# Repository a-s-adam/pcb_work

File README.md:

Working with JDM product development structures, it's hard to get full exposure on an entire electrical PCB design from start to finish. The goal of this repository is to display design, component selection, schematic capture, layout, ordering, and bring-up without sharing designs done during my 9-5 job.

dev_board
- Working to redefine scope of this board; originally it was ATMEGA which is less common in production boards, so I'm exploring ESP32 based system to make an IoT mesh network.
- [Work in Progress]

MixSigBoard
- STM32 Based board with 2 SPI interfaces (ADC,DAC), ADC input, DAC output, a few GPIO's via RGB LED's, and Software Debug (SWD) interface.
- Analog Bias Generator, anti-aliasing filters, power supply line filtering, USB-C 2.0 compatibility
- Ground via next to all signal vias to give short return path and reduce EMI
- Fan out of traces where possible to reduce cross talk
- PHYSICAL separation of analog and digital components (placing A&D components far apart from each other has best results of reducing noise between the two) https://www.youtube.com/watch?v=ySuUZEjARPY
- Stitching Vias placed throughout board (2.5 mm grid)
- Silkscreen labeling of circuit portions
- Included Gerber, BOM, footprints,symbols, drill files

FPGA_Board
- AMD Zynq-7000 based board: https://docs.amd.com/v/u/en-US/zynq-7000-product-selection-guide [XC7Z010-2CLG400I]
- Config Memory is determined by FPGA chosen: https://docs.amd.com/r/en-US/ug908-vivado-programming-debugging/Virtex-UltraScale-Configuration-Memory-Devices?tocId=SfnAO9Qdpk7bcqPQwSsYiQ
- BGA Routing Application Manual: https://docs.amd.com/r/en-US/ug1099-bga-device-design-rules/Introduction
- Stack-up Selection for Various Layer PCB's https://www.pcbway.com/multi-layer-laminated-structure.html
- [Work in Progress]

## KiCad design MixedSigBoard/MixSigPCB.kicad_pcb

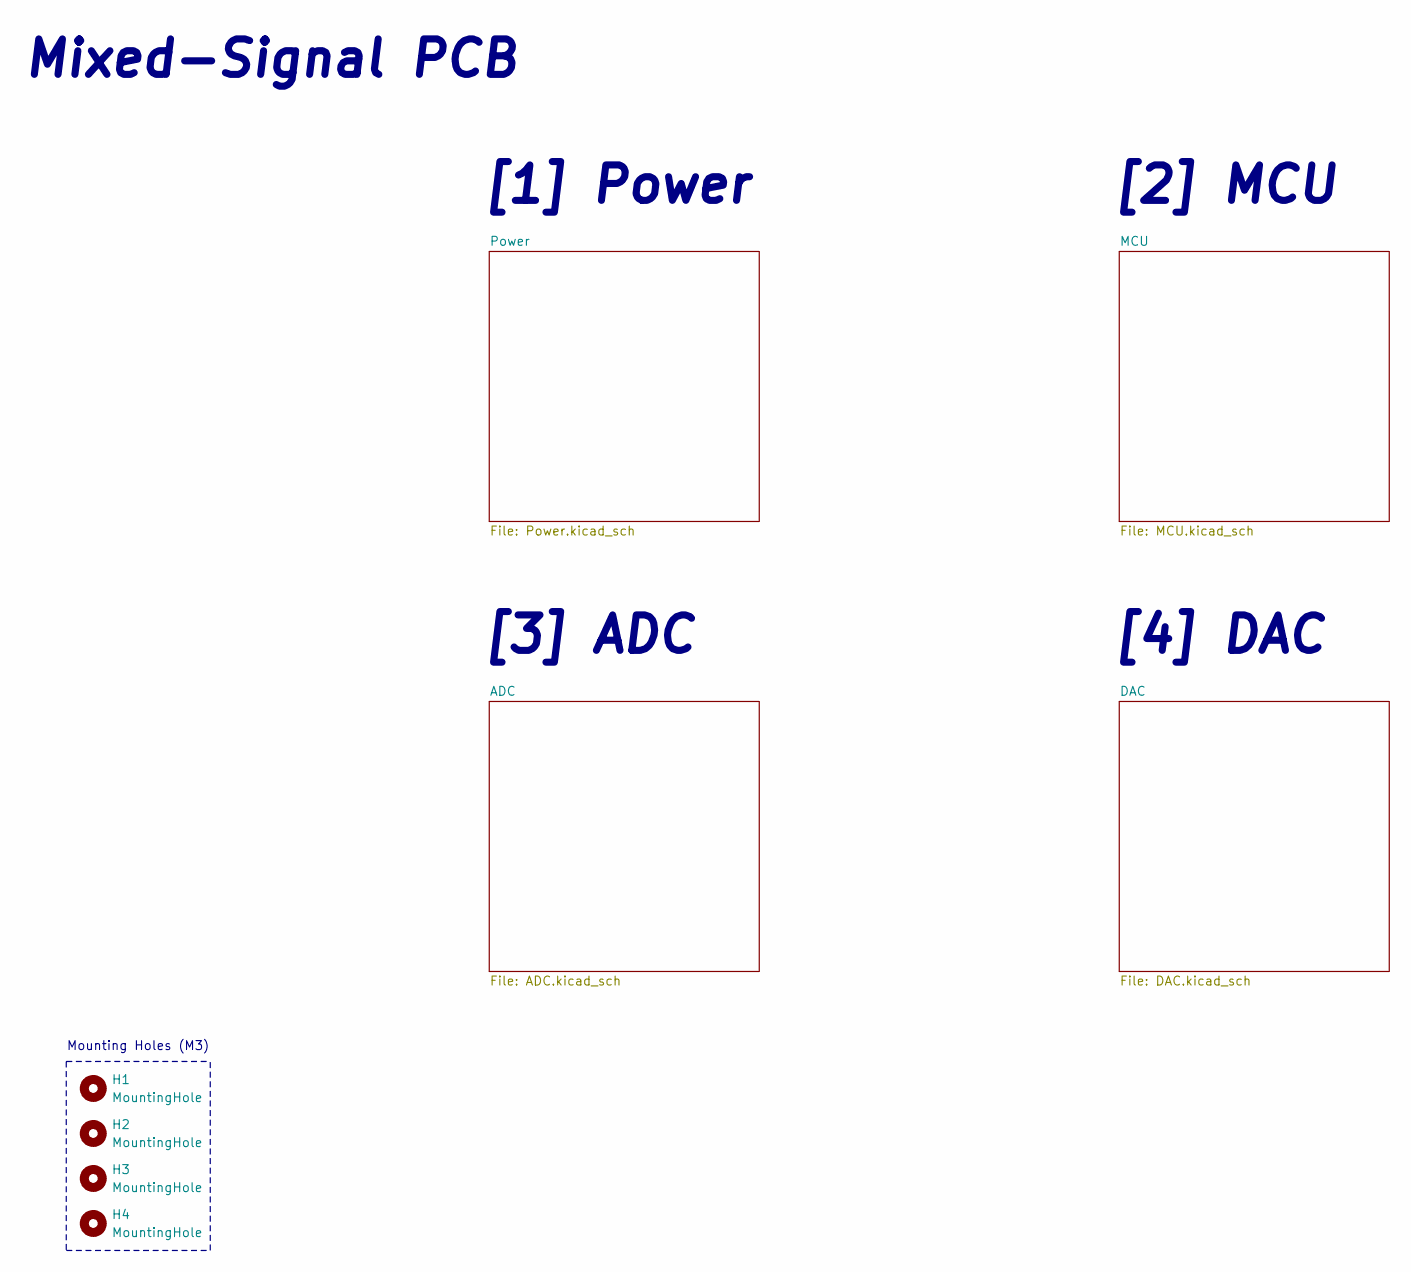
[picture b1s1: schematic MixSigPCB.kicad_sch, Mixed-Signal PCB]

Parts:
H1, H2, H3, H4: MountingHole; MountingHole_3.2mm_M3

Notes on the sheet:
[4] DAC
Mixed-Signal PCB
[3] ADC
Mounting Holes (M3)
[2] MCU
[1] Power

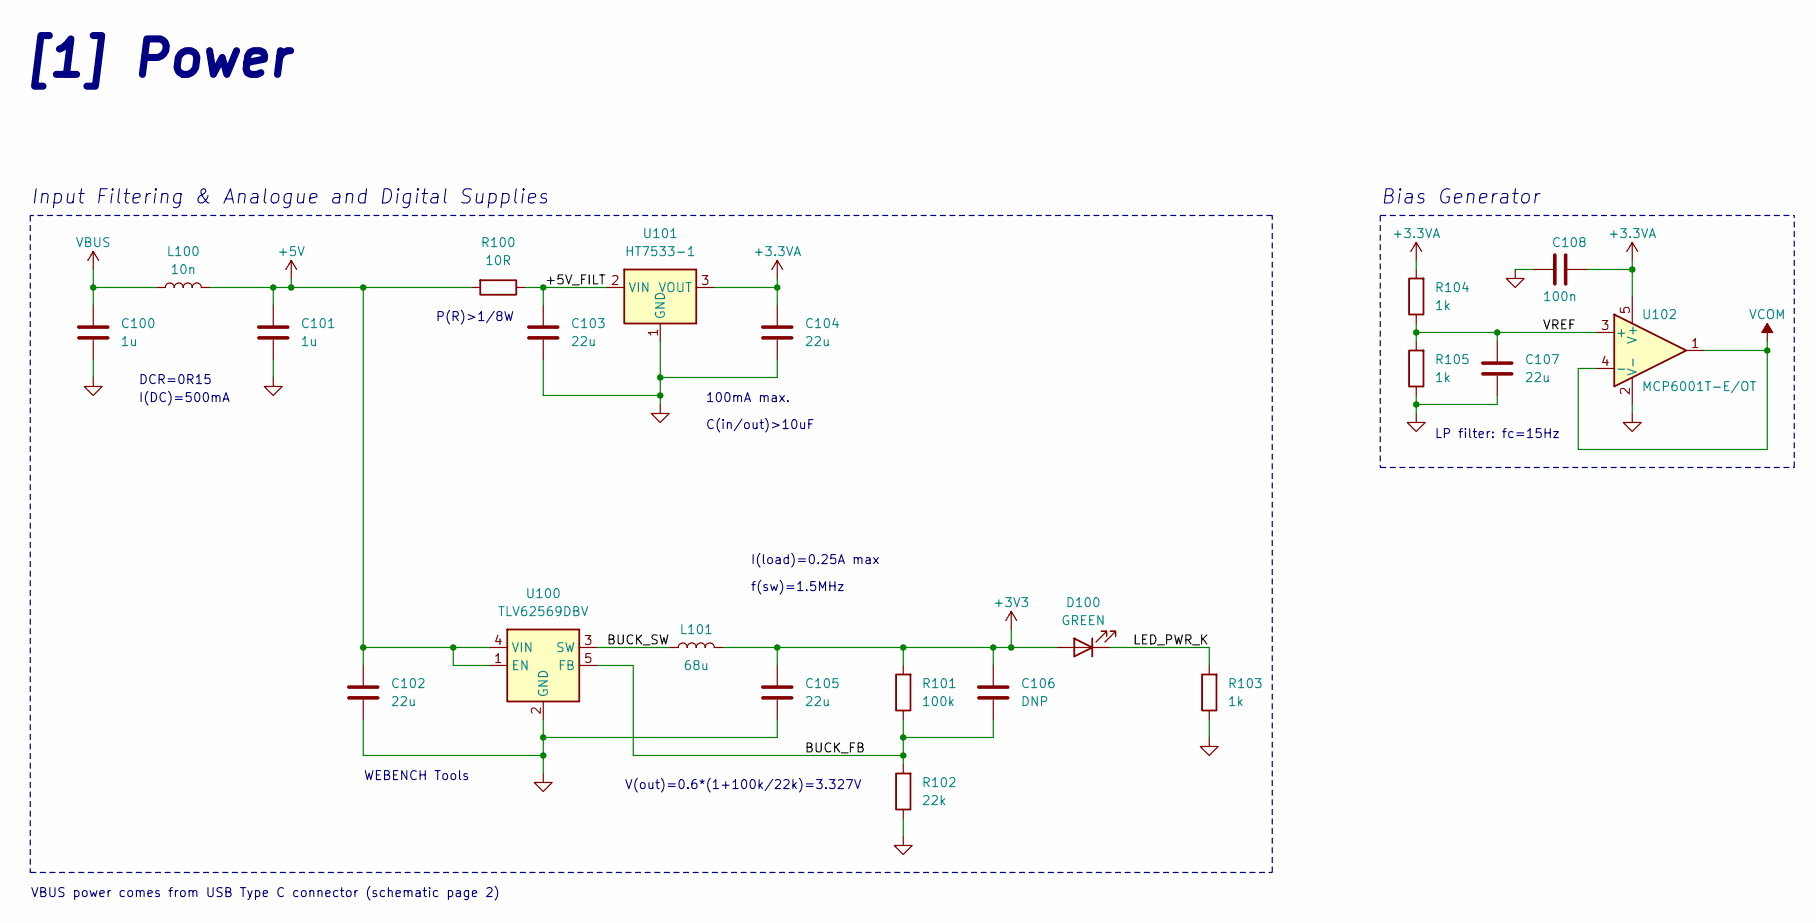
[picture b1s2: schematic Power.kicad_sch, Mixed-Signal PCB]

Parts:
C100, C101: 1u; C_0603_1608Metric; Manufacturer Part Number CC0603KRX5R6BB105
C102, C103, C104, C105, C107: 22u; C_0805_2012Metric; Manufacturer Part Number GRM21BZ71A226ME15L
C106: DNP; C_0402_1005Metric
C108: 100n; C_0402_1005Metric; Manufacturer Part Number LMK105B7104KVHF
D100: GREEN; LED_0603_1608Metric; Manufacturer Part Number APT1608ZGC-AMT
L100: 10n; L_0402_1005Metric; Manufacturer Part Number BLM15BX601SZ1D
L101: 68u; MWSA0603S; Manufacturer Part Number MWSA0603S-100MT
R100: 10R; R_0805_2012Metric; Manufacturer Part Number 0805W8F100JT5E
R101: 100k; R_0402_1005Metric; Manufacturer Part Number 0402WGJ0104TCE
R102: 22k; R_0402_1005Metric; Manufacturer Part Number 0402WGJ0223TCE
R103, R104, R105: 1k; R_0402_1005Metric; Manufacturer Part Number 0402WGF1001TCE
U100: TLV62569DBV; SOT-23-5; Manufacturer Part Number TLV62569DBVT
U101: HT7533-1; SOT-89-3; Manufacturer Part Number HT7533-1
U102: MCP6001T-E/OT; SOT-23-5; Manufacturer Part Number MCP6001T-E/OT

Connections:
+3.3VA: C104.1, C108.1, R104.2, U101.3 (VOUT), U102.5 (V+); also elsewhere on the board
+3V3: C105.1, C106.1, D100.2 (A), L101.2, R101.2; also elsewhere on the board
+5V: C101.1, C102.1, L100.2, R100.2, U100.1 (EN), U100.4 (VIN); also elsewhere on the board
/Power/+5V_FILT: C103.1, R100.1, U101.2 (VIN)
/Power/BUCK_FB: C106.2, R101.1, R102.2, U100.5 (FB)
/Power/BUCK_SW: L101.1, U100.3 (SW)
/Power/LED_PWR_K: D100.1 (K), R103.2
/Power/VREF: C107.1, R104.1, R105.2, U102.3 (+)
GND: C100.2, C101.2, C102.2, C103.2, C104.2, C105.2, C107.2, C108.2, R102.1, R103.1, R105.1, U100.2 (GND), U101.1 (GND), U102.2 (V-); also elsewhere on the board
VBUS: C100.1, L100.1; also elsewhere on the board
VCOM: U102.1, U102.4 (-); also elsewhere on the board

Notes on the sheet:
DCR=0R15
C(in/out)>10uF
V(out)=0.6*(1+100k/22k)=3.327V
I(DC)=500mA
Bias Generator
LP filter: fc=15Hz
100mA max.
f(sw)=1.5MHz
VBUS power comes from USB Type C connector (schematic page 2)
P(R)>1/8W
I(load)=0.25A max
Input Filtering & Analogue and Digital Supplies
[1] Power
WEBENCH Tools

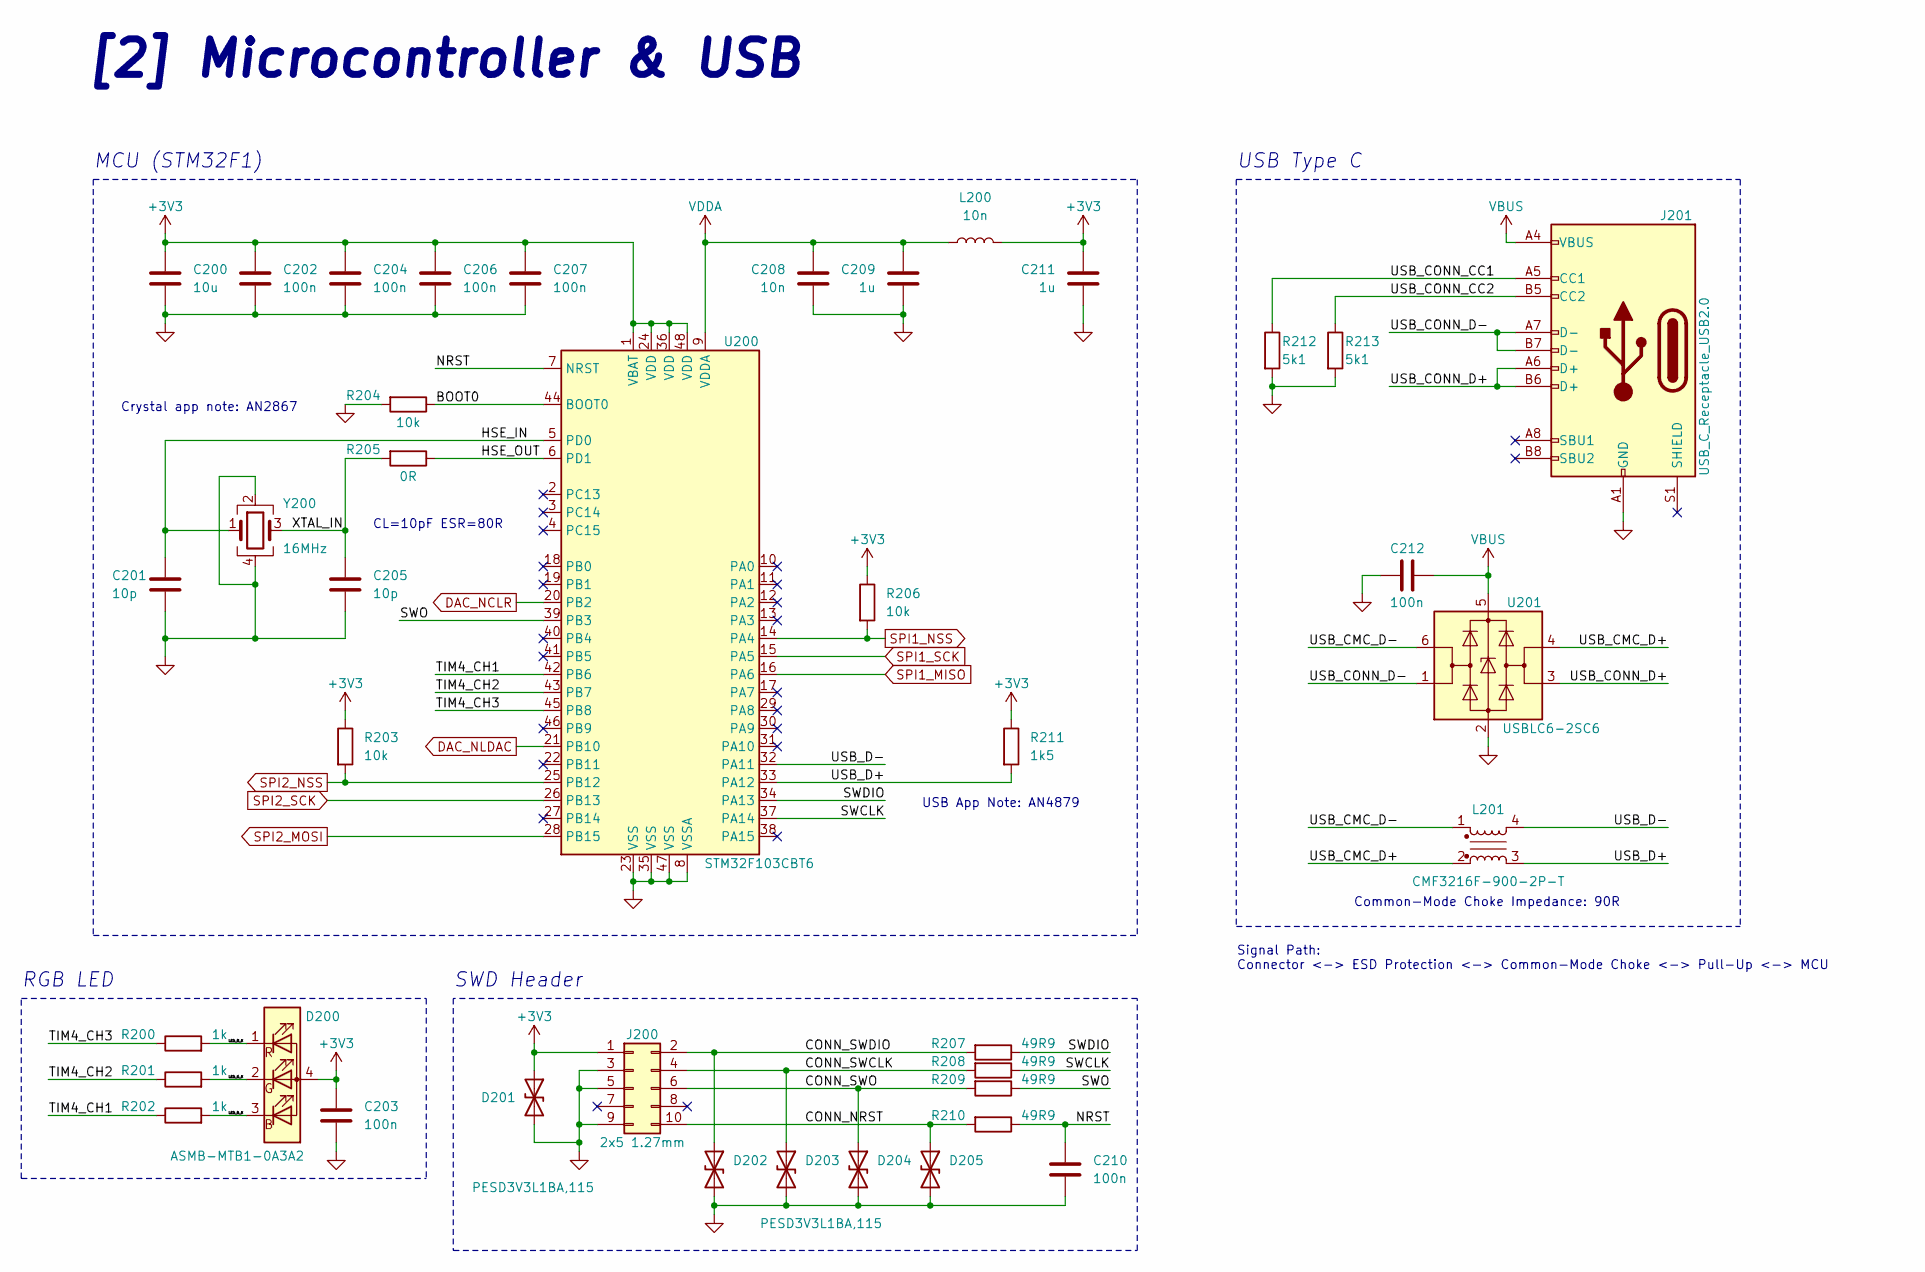
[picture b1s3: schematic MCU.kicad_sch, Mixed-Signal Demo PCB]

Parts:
C200: 10u; C_0603_1608Metric; Manufacturer Part Number MLASL168BB5106MTNB33
C201, C205: 10p; C_0402_1005Metric; Manufacturer Part Number KAM05ACG1H100JH
C202, C203, C204, C206, C207, C210, C212: 100n; C_0402_1005Metric; Manufacturer Part Number LMK105B7104KVHF
C208: 10n; C_0402_1005Metric; Manufacturer Part Number GRM022C81C103ME01L
C209, C211: 1u; C_0603_1608Metric; Manufacturer Part Number CC0603KRX5R6BB105
D200: ASMB-MTB1-0A3A2; LED_Avago_PLCC4_3.2x2.8mm_CW; Manufacturer Part Number OVSARGB4R8
D201, D202, D203, D204, D205: PESD3V3L1BA,115; D_SOD-323; Manufacturer Part Number PESD3V3L1BA,115
J200: 2x5 1.27mm; PinHeader_2x05_P1.27mm_Vertical_SMD; Manufacturer Part Number 3220-10-0100-00
J201: USB_C_Receptacle_USB2.0; USB_C_Receptacle_HRO_TYPE-C-31-M-12; Manufacturer Part Number TYPE-C-31-M-12
L200: 10n; L_0402_1005Metric; Manufacturer Part Number BLM15BX601SZ1D
L201: CMF3216F-900-2P-T; CMC-1206; Manufacturer Part Number CMF3216F-900-2P-T
R200, R201, R202: 1k; R_0402_1005Metric; Manufacturer Part Number 0402WGF1001TCE
R203, R204, R206: 10k; R_0402_1005Metric; Manufacturer Part Number 0402WGF1002TCE
R205: 0R; R_0402_1005Metric; Manufacturer Part Number 0402WGF0000TCE
R207, R208, R209, R210: 49R9; R_0402_1005Metric; Manufacturer Part Number 0402WGF499JTCE
R211: 1k5; R_0402_1005Metric; Manufacturer Part Number 0402WGF1501TCE
R212, R213: 5k1; R_0402_1005Metric; Manufacturer Part Number 0402WGF5101TCE
U200: STM32F103CBT6; LQFP-48_7x7mm_P0.5mm; Manufacturer Part Number STM32F103CBT6
U201: USBLC6-2SC6; SOT-23-6; Manufacturer Part Number USBLC6-2SC6
Y200: 16MHz; Crystal_SMD_3225-4Pin_3.2x2.5mm; Manufacturer Part Number TSX-3225 16.0000MF09Z-AC3

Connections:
+3V3: C200.1, C202.1, C203.1, C204.1, C206.1, C207.1, C211.1, D200.4 (A), D201.1 (A1), J200.1, L200.2, R203.1, R206.1, R211.1, U200.1 (VBAT), U200.24 (VDD), U200.36 (VDD), U200.48 (VDD); also elsewhere on the board
/MCU/BOOT0: R204.1, U200.44 (BOOT0)
/MCU/CONN_NRST: D205.1 (A1), J200.10, R210.2
/MCU/CONN_SWCLK: D203.1 (A1), J200.4, R208.2
/MCU/CONN_SWDIO: D202.1 (A1), J200.2, R207.2
/MCU/CONN_SWO: D204.1 (A1), J200.6, R209.2
/MCU/HSE_IN: C201.1, U200.5 (PD0), Y200.1
/MCU/HSE_OUT: R205.1, U200.6 (PD1)
/MCU/LED_B_K: D200.3 (BK), R202.2
/MCU/LED_G_K: D200.2 (GK), R201.2
/MCU/LED_R_K: D200.1 (RK), R200.2
/MCU/NRST: C210.1, R210.1, U200.7 (NRST)
/MCU/SWCLK: R208.1, U200.37 (PA14)
/MCU/SWDIO: R207.1, U200.34 (PA13)
/MCU/SWO: R209.1, U200.39 (PB3)
/MCU/TIM4_CH1: R202.1, U200.42 (PB6)
/MCU/TIM4_CH2: R201.1, U200.43 (PB7)
/MCU/TIM4_CH3: R200.1, U200.45 (PB8)
/MCU/USB_CMC_D+: L201.2, U201.4 (I/O2)
/MCU/USB_CMC_D-: L201.1, U201.6 (I/O1)
/MCU/USB_CONN_CC1: J201.A5 (CC1), R212.1
/MCU/USB_CONN_CC2: J201.B5 (CC2), R213.1
/MCU/USB_CONN_D+: J201.A6 (D+), J201.B6 (D+), U201.3 (I/O2)
/MCU/USB_CONN_D-: J201.A7 (D-), J201.B7 (D-), U201.1 (I/O1)
/MCU/USB_D+: L201.3, R211.2, U200.33 (PA12)
/MCU/USB_D-: L201.4, U200.32 (PA11)
/MCU/XTAL_IN: C205.1, R205.2, Y200.3
DAC_NCLR: U200.20 (PB2); also elsewhere on the board
DAC_NLDAC: U200.21 (PB10); also elsewhere on the board
GND: C200.2, C201.2, C202.2, C203.2, C204.2, C205.2, C206.2, C207.2, C208.2, C209.2, C210.2, C211.2, C212.2, D201.2 (A2), D202.2 (A2), D203.2 (A2), D204.2 (A2), D205.2 (A2), J200.3, J200.5, J200.9, J201.A1 (GND), J201.A12 (GND), J201.B1 (GND), J201.B12 (GND), R204.2, R212.2, R213.2, U200.8 (VSSA), U200.23 (VSS), U200.35 (VSS), U200.47 (VSS), U201.2 (GND), Y200.2, Y200.4; also elsewhere on the board
SPI1_MISO: U200.16 (PA6); also elsewhere on the board
SPI1_NSS: R206.2, U200.14 (PA4); also elsewhere on the board
SPI1_SCK: U200.15 (PA5); also elsewhere on the board
SPI2_MOSI: U200.28 (PB15); also elsewhere on the board
SPI2_NSS: R203.2, U200.25 (PB12); also elsewhere on the board
SPI2_SCK: U200.26 (PB13); also elsewhere on the board
VBUS: C212.1, J201.A4 (VBUS), J201.A9 (VBUS), J201.B4 (VBUS), J201.B9 (VBUS), U201.5 (VBUS); also elsewhere on the board
VDDA: C208.1, C209.1, L200.1, U200.9 (VDDA)

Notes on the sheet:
Signal Path: Connector <-> ESD Protection <-> Common-Mode Choke <-> Pull-Up <-> MCU
RGB LED
Crystal app note: AN2867
SWD Header
USB App Note: AN4879
Common-Mode Choke Impedance: 90R
[2] Microcontroller & USB
CL=10pF ESR=80R
MCU (STM32F1)
USB Type C

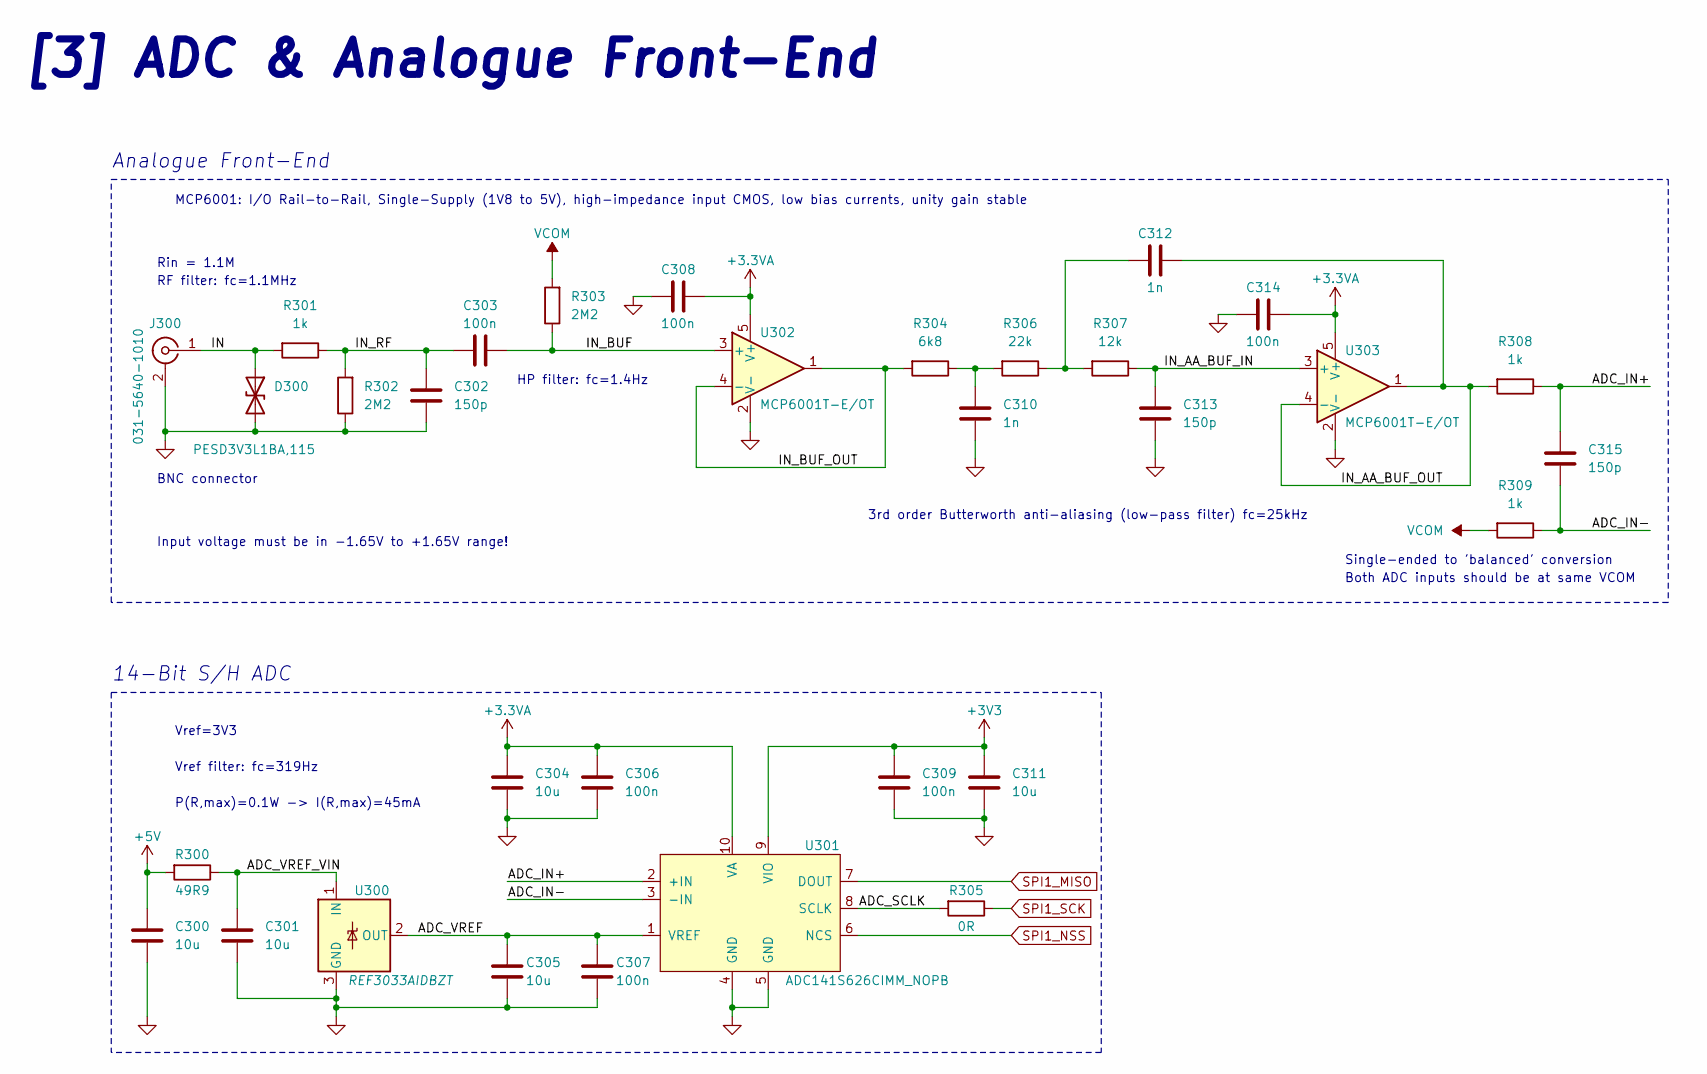
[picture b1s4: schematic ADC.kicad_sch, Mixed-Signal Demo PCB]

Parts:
C300, C301, C304, C305, C311: 10u; C_0603_1608Metric; Manufacturer Part Number MLASL168BB5106MTNB33
C302, C313, C315: 150p; C_0402_1005Metric; Manufacturer Part Number C0402C151J1GACAUTO
C303, C306, C307, C308, C309, C314: 100n; C_0402_1005Metric; Manufacturer Part Number LMK105B7104KVHF
C310, C312: 1n; C_0402_1005Metric; Manufacturer Part Number 04025C102KAZ2A
D300: PESD3V3L1BA,115; D_SOD-323; Manufacturer Part Number PESD3V3L1BA,115
J300: 031-5640-1010; AMPHENOL-BNC-031-5640-1010; Manufacturer Part Number 31-5640-1010
R300: 49R9; R_0402_1005Metric; Manufacturer Part Number 0402WGF499JTCE
R301, R308, R309: 1k; R_0402_1005Metric; Manufacturer Part Number 0402WGF1001TCE
R302, R303: 2M2; R_0402_1005Metric; Manufacturer Part Number RC0402FR-072M2L
R304: 6k8; R_0402_1005Metric; Manufacturer Part Number 0402WGF6801TCE
R305: 0R; R_0402_1005Metric; Manufacturer Part Number 0402WGF0000TCE
R306: 22k; R_0402_1005Metric; Manufacturer Part Number 0402WGJ0223TCE
R307: 12k; R_0402_1005Metric; Manufacturer Part Number 0402WGJ0123TCE
U300: REF3033AIDBZT; SOT-23; Manufacturer Part Number REF3033AIDBZT
U301: ADC141S626CIMM_NOPB; VSSOP-10; Manufacturer Part Number ADC141S626CIMM/NOPB
U302, U303: MCP6001T-E/OT; SOT-23-5; Manufacturer Part Number MCP6001T-E/OT

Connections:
+3.3VA: C304.1, C306.1, C308.1, C314.1, U301.10 (VA), U302.5 (V+), U303.5 (V+); also elsewhere on the board
+3V3: C309.1, C311.1, U301.9 (VIO); also elsewhere on the board
+5V: C300.1, R300.2; also elsewhere on the board
/ADC/ADC_IN+: C315.1, R308.1, U301.2 (+IN)
/ADC/ADC_IN-: C315.2, R309.1, U301.3 (-IN)
/ADC/ADC_SCLK: R305.2, U301.8 (SCLK)
/ADC/ADC_VREF: C305.1, C307.1, U300.2 (OUT), U301.1 (VREF)
/ADC/ADC_VREF_VIN: C301.1, R300.1, U300.1 (IN)
/ADC/IN: D300.1 (A1), J300.1 (In), R301.2
/ADC/IN_AA_BUF_IN: C313.1, R307.1, U303.3 (+)
/ADC/IN_AA_BUF_OUT: C312.2, R308.2, U303.1, U303.4 (-)
/ADC/IN_BUF: C303.1, R303.1, U302.3 (+)
/ADC/IN_BUF_OUT: R304.2, U302.1, U302.4 (-)
/ADC/IN_RF: C302.1, C303.2, R301.1, R302.2
GND: C300.2, C301.2, C302.2, C304.2, C305.2, C306.2, C307.2, C308.2, C309.2, C310.2, C311.2, C313.2, C314.2, D300.2 (A2), J300.2 (Ext), R302.1, U300.3 (GND), U301.4 (GND), U301.5 (GND), U302.2 (V-), U303.2 (V-); also elsewhere on the board
unnamed: C310.1, R304.1, R306.2
unnamed: C312.1, R306.1, R307.2
SPI1_MISO: U301.7 (DOUT); also elsewhere on the board
SPI1_NSS: U301.6 (NCS); also elsewhere on the board
SPI1_SCK: R305.1; also elsewhere on the board
VCOM: R303.2, R309.2; also elsewhere on the board

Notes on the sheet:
HP filter: fc=1.4Hz
Both ADC inputs should be at same VCOM
BNC connector
Rin = 1.1M
14-Bit S/H ADC
Vref filter: fc=319Hz
Input voltage must be in -1.65V to +1.65V range!
Analogue Front-End
Single-ended to 'balanced' conversion
RF filter: fc=1.1MHz
3rd order Butterworth anti-aliasing (low-pass filter) fc=25kHz
MCP6001: I/O Rail-to-Rail, Single-Supply (1V8 to 5V), high-impedance input CMOS, low bias currents, unity gain stable
P(R,max)=0.1W -> I(R,max)=45mA
Vref=3V3
[3] ADC & Analogue Front-End

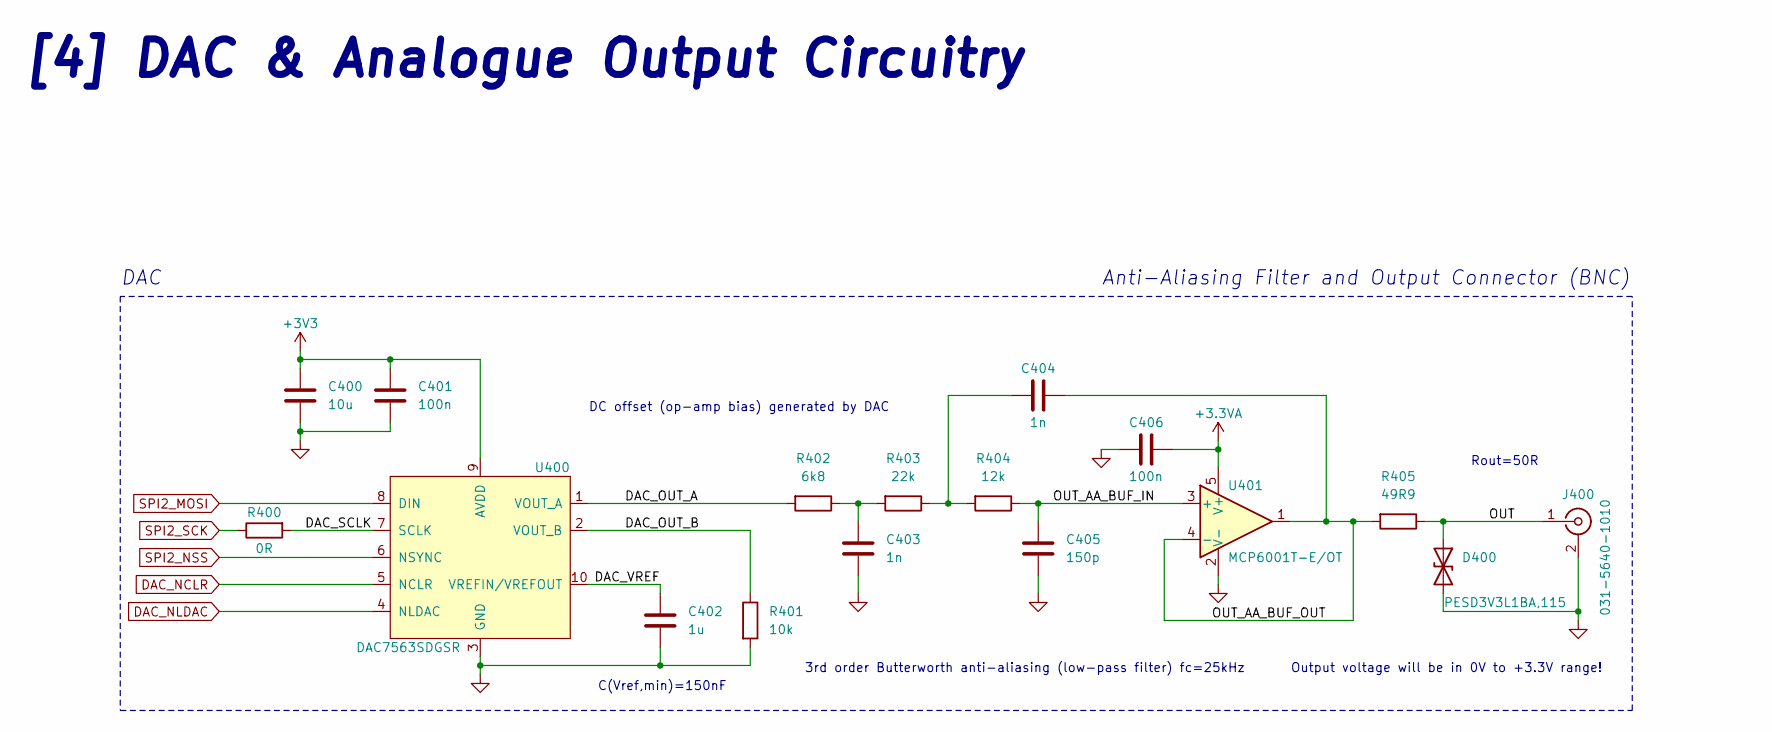
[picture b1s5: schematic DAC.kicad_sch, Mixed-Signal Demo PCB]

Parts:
C400: 10u; C_0603_1608Metric; Manufacturer Part Number MLASL168BB5106MTNB33
C401, C406: 100n; C_0402_1005Metric; Manufacturer Part Number LMK105B7104KVHF
C402: 1u; C_0603_1608Metric; Manufacturer Part Number CC0603KRX5R6BB105
C403, C404: 1n; C_0402_1005Metric; Manufacturer Part Number 04025C102KAZ2A
C405: 150p; C_0402_1005Metric; Manufacturer Part Number C0402C151J1GACAUTO
D400: PESD3V3L1BA,115; D_SOD-323; Manufacturer Part Number PESD3V3L1BA,115
J400: 031-5640-1010; AMPHENOL-BNC-031-5640-1010; Manufacturer Part Number 31-5640-1010
R400: 0R; R_0402_1005Metric; Manufacturer Part Number 0402WGF0000TCE
R401: 10k; R_0402_1005Metric; Manufacturer Part Number 0402WGF1002TCE
R402: 6k8; R_0402_1005Metric; Manufacturer Part Number 0402WGF6801TCE
R403: 22k; R_0402_1005Metric; Manufacturer Part Number 0402WGJ0223TCE
R404: 12k; R_0402_1005Metric; Manufacturer Part Number 0402WGJ0123TCE
R405: 49R9; R_0402_1005Metric; Manufacturer Part Number 0402WGF499JTCE
U400: DAC7563SDGSR; VSSOP-10; Manufacturer Part Number DAC7563SDGSR
U401: MCP6001T-E/OT; SOT-23-5; Manufacturer Part Number MCP6001T-E/OT

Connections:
+3.3VA: C406.1, U401.5 (V+); also elsewhere on the board
+3V3: C400.1, C401.1, U400.9 (AVDD); also elsewhere on the board
/DAC/DAC_OUT_A: R402.2, U400.1 (VOUT_A)
/DAC/DAC_OUT_B: R401.1, U400.2 (VOUT_B)
/DAC/DAC_SCLK: R400.2, U400.7 (SCLK)
/DAC/DAC_VREF: C402.1, U400.10 (VREFIN/VREFOUT)
/DAC/OUT: D400.1 (A1), J400.1 (In), R405.1
/DAC/OUT_AA_BUF_IN: C405.1, R404.1, U401.3 (+)
/DAC/OUT_AA_BUF_OUT: C404.2, R405.2, U401.1, U401.4 (-)
DAC_NCLR: U400.5 (NCLR); also elsewhere on the board
DAC_NLDAC: U400.4 (NLDAC); also elsewhere on the board
GND: C400.2, C401.2, C402.2, C403.2, C405.2, C406.2, D400.2 (A2), J400.2 (Ext), R401.2, U400.3 (GND), U401.2 (V-); also elsewhere on the board
unnamed: C403.1, R402.1, R403.2
unnamed: C404.1, R403.1, R404.2
SPI2_MOSI: U400.8 (DIN); also elsewhere on the board
SPI2_NSS: U400.6 (NSYNC); also elsewhere on the board
SPI2_SCK: R400.1; also elsewhere on the board

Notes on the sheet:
[4] DAC & Analogue Output Circuitry
Anti-Aliasing Filter and Output Connector (BNC)
Rout=50R
Output voltage will be in 0V to +3.3V range!
DAC
C(Vref,min)=150nF
3rd order Butterworth anti-aliasing (low-pass filter) fc=25kHz
DC offset (op-amp bias) generated by DAC

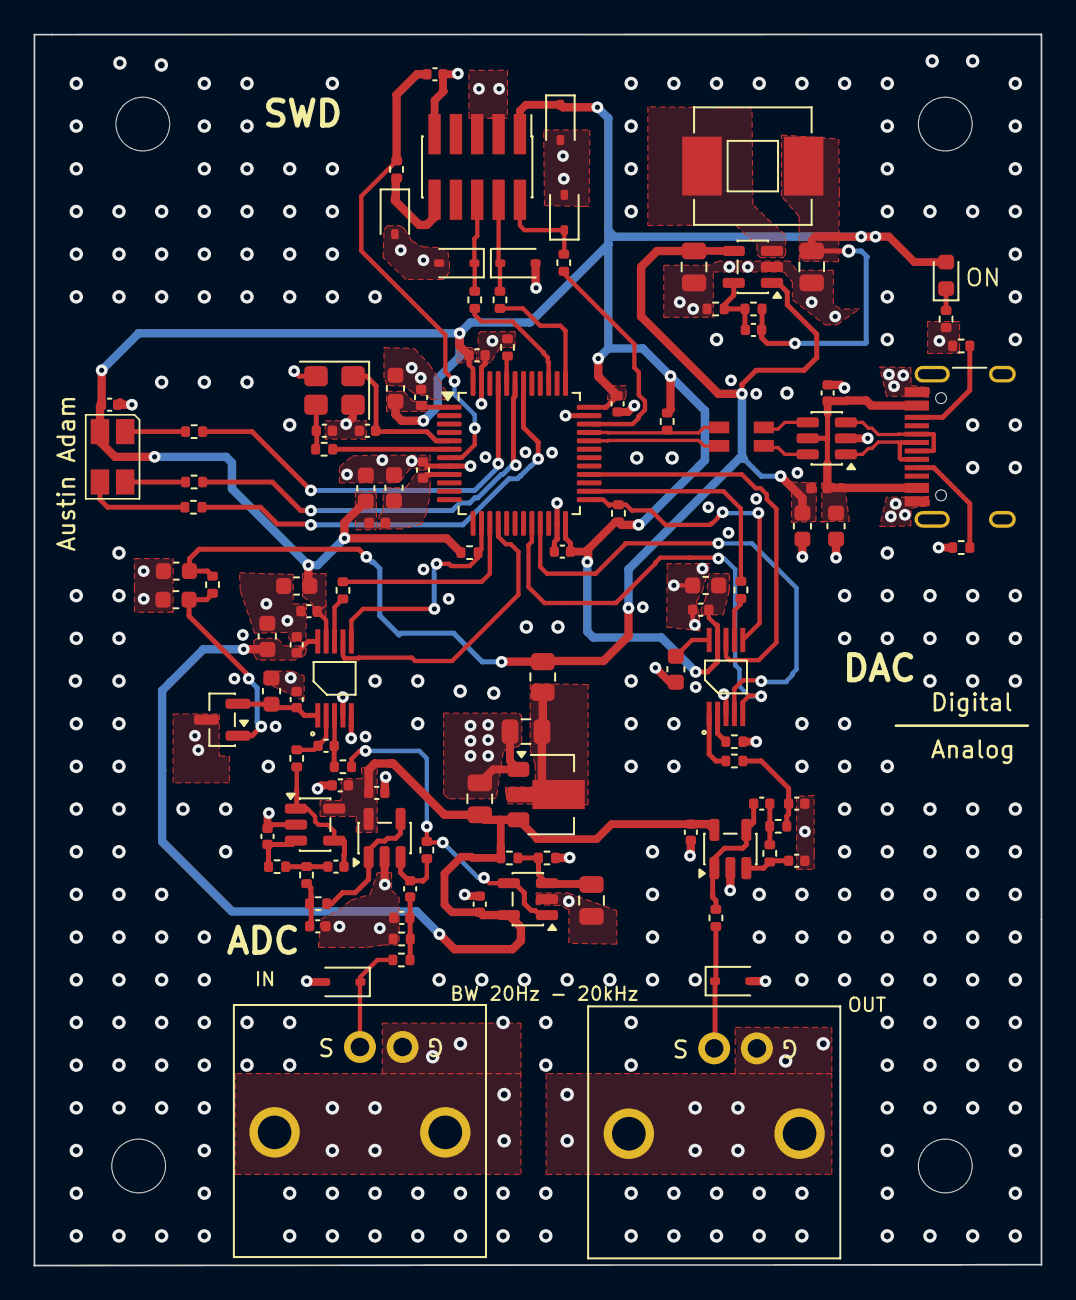
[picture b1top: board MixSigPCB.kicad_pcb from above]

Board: 4 copper layers, 59.9 x 73.3 mm, 114 parts (0 on the bottom side), 68 nets.

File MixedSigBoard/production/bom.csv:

Designator,Footprint,Quantity,Value,LCSC Part #
"C100, C101, C209, C211, C402",0603,5,1u,
"C102, C103, C104, C105, C107",0805,5,22u,
C106,0402,1,DNP,
"C108, C202, C203, C204, C206, C207, C210, C212, C303, C306, C307, C308, C309, C314, C401, C406",0402,16,100n,
"C200, C300, C301, C304, C305, C311, C400",0603,7,10u,
"C201, C205",0402,2,10p,
"C208, L100, L200",0402,3,10n,
"C302, C313, C315, C405",0402,4,150p,
"C310, C312, C403, C404",0402,4,1n,
D100,0603,1,GREEN,
D200,LED_Avago_PLCC4_3.2x2.8mm_CW,1,ASMB-MTB1-0A3A2,
"D201, D202, D203, D204, D205, D300, D400",D_SOD-323,7,"PESD3V3L1BA,115",
"H1, H2, H3, H4",MountingHole_3.2mm_M3,4,MountingHole,
J200,PinHeader_2x05_P1.27mm_Vertical_SMD,1,2x5 1.27mm,
J201,USB_C_Receptacle_HRO_TYPE-C-31-M-12,1,USB_C_Receptacle_USB2.0,
"J300, J400",AMPHENOL-BNC-031-5640-1010,2,031-5640-1010,
L101,MWSA0603S,1,68u,
L201,CMC-1206,1,CMF3216F-900-2P-T,
R100,0805,1,10R,
R101,0402,1,100k,
"R102, R306, R403",0402,3,22k,
"R103, R104, R105, R200, R201, R202, R301, R308, R309",0402,9,1k,
"R203, R204, R206, R401",0402,4,10k,
"R205, R305, R400",0402,3,0R,
"R207, R208, R209, R210, R300, R405",0402,6,49R9,
R211,0402,1,1k5,
"R212, R213",0402,2,5k1,
"R302, R303",0402,2,2M2,
"R304, R402",0402,2,6k8,
"R307, R404",0402,2,12k,
U100,SOT-23-5,1,TLV62569DBV,
U101,SOT-89-3,1,HT7533-1,
"U102, U302, U303, U401",SOT-23-5,4,MCP6001T-E/OT,
U200,LQFP-48_7x7mm_P0.5mm,1,STM32F103CBT6,
U201,SOT-23-6,1,USBLC6-2SC6,
U300,SOT-23,1,REF3033AIDBZT,
U301,VSSOP-10,1,ADC141S626CIMM_NOPB,
U400,VSSOP-10,1,DAC7563SDGSR,
Y200,Crystal_SMD_3225-4Pin_3.2x2.5mm,1,16MHz,

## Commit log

2025-03-29 Remove tracked .lck file
2025-03-29 created project directory structure
2025-03-29 removed personal metadata files
2025-03-29 circuit changes - ESD protection, ISP connection, status LED's, decoupling
2025-04-03 oscillator
2025-04-03 fix merge
2025-04-03 schematic autosave issue
2025-04-06 UART IC + test switches + extra LED's
2025-07-14 initial commit for wifi board
2025-11-27 Mixed Signal Board
2025-11-28 Add hierarchical sheets & footprints
2025-11-30 Change Buck Inductor
2025-12-01 Added footprints, created schematic, added LTspice simulation for 3rd order filter shown in DAC/ADC
2025-12-07 -Renumber components to match sheet number -Created PCB Constraints and Set-up
2025-12-12 Add all footprints
2025-12-13 add pcb footprints
2025-12-13 add pcb footprint
2025-12-13 Layout w/o Traces for MCU, ADC page
2025-12-15 Finished general PCB placement
2025-12-16 updated PCB footprints
2025-12-18 add routing to SWD,RGB LED's, USB, partial buck, partial power decoupling
    - Copper pours to lower inductance/EMI/better return current
    - Differential traces on USB, 50ohm single ended for SPI & for all signal lines for good practice
    - Grounding via's near ground pin and slightly towards power side to minimize return path
2025-12-20 add routing for 1 of 2 analog portions
    - 50 ohm trace routing for analog portion
    - adc portion routing finished (except POWER routing)
2025-12-21 add DAC routing, power routing, finish routing
    - finished routing, cleared up most DRC errors
    - Removed reference designators on F. Silkscreen
2025-12-22 Add missing footprints
2025-12-23 Include Gerber and Assembly parts except BOM
2025-12-23 complete the MixSigPCB
    -Created Gerber file and compressed to .zip
    -created placement file
    -filled all components from Mouser/JLCPCB/Digikey
2025-12-23 complete the MixSigPCB
2025-12-23 Fix drill + grid origin
2025-12-23 Fix excess ground pour on outer board
2025-12-24 Initial commit for FPGA Board
2025-12-24 Update README.md FPGA_Board
2025-12-25 Create Block Diagram, create Vivado Project
2025-12-26 Create block diagram & QSPI footprint
2025-12-31 Add XPE Xilinx sheet for SoC power consumption
2026-01-04 Add Xilinx reference guides for FPGA PCB Design
2026-01-07 Add photos of final board layout
2026-01-07 update .gitignore to not consider -backups/
2026-01-07 add fp-info-cache
2026-01-17 Add comprehensive ignore for KiCad, FPGA, and tooling artifacts
2026-04-17 - remove legacy design
2026-04-17 add dev_board hierarchical sheets
2026-04-18 - modify USB connector design in FPGA Board
2026-04-20 Add symbols and rename vivado project for clarity
2026-04-20 fix 'USB 3.0' typo, add USB C connector and eFuse
2026-04-23 wire eFuse and USB-C, add global labels for USB D+/D-
2026-04-26 Add fabrication & assembly files, specific format for JLCPCB
2026-04-26 add FPGA,DDR, Decoupling capacitor symbols for power & ddr sheets. modify symbols pinout placement to clean up schematic
2026-04-27 Add DDR VTT power module, add Zynq power + decoupling, placed Zynq DDR
